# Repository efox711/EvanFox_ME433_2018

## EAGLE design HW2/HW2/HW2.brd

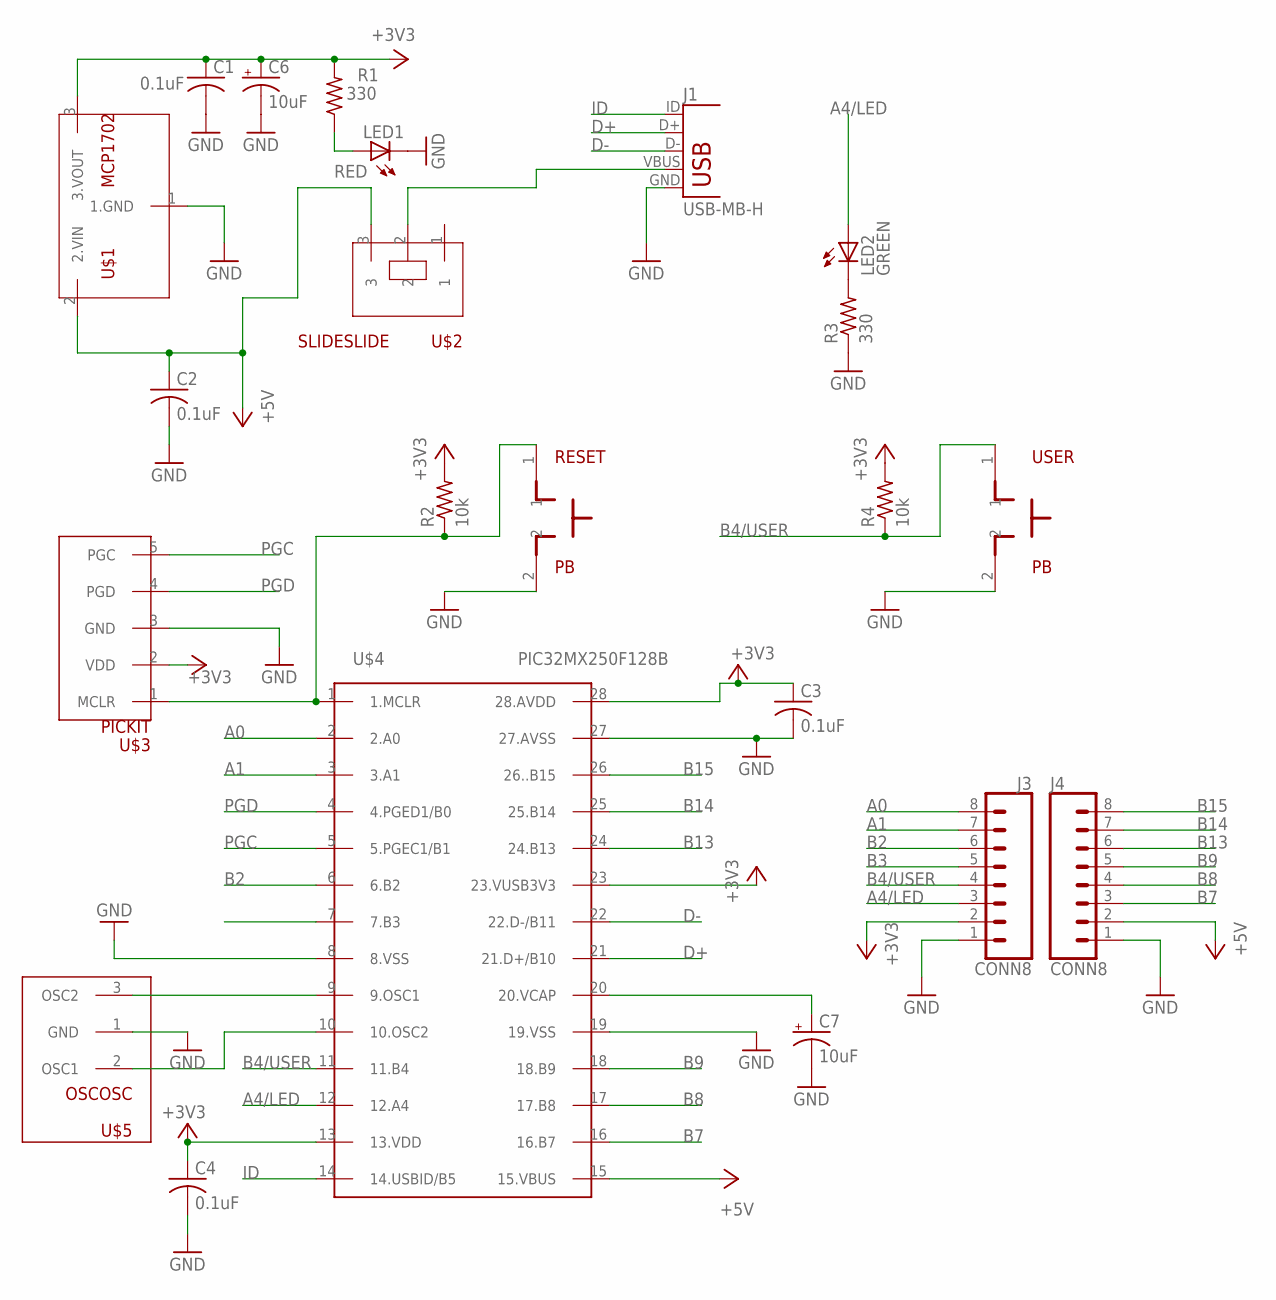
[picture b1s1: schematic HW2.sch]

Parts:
C1, C2, C3, C4: 0.1uF; C025-025X050
C6, C7: 10uF; B45181B
J1: USB-MB-H
J3, J4: CONN8; 1X08
LED1: RED; LED3MM
LED2: GREEN; LED3MM
R1, R3: 330; 0207/10
R2, R4: 10k; 0207/10
RESET: PB
U$1: MCP1702; TO92
U$2: SLIDESLIDE; SLIDE
U$3: PICKIT; 1X05
U$4: PIC32MX250F128B; DIL28-3
U$5: OSCOSC; OSC
USER: PB

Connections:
+3V3: C1.1, C3.1, C4.1, C6.+, J3.2, R1.2, R2.2, R4.2, U$1.3 (3.VOUT), U$3.2 (VDD), U$4.13 (13.VDD), U$4.23 (23.VUSB3V3), U$4.28 (28.AVDD)
+5V: C2.1, J4.2, U$1.2 (2.VIN), U$2.3, U$4.15 (15.VBUS)
A0: J3.8, U$4.2 (2.A0)
A1: J3.7, U$4.3 (3.A1)
A4/LED: J3.3, LED2.A, U$4.12 (12.A4)
B2: J3.6, U$4.6 (6.B2)
B3: J3.5, U$4.7 (7.B3)
B4/USER: J3.4, R4.1, U$4.11 (11.B4), USER.1
B7: J4.3, U$4.16 (16.B7)
B8: J4.4, U$4.17 (17.B8)
B9: J4.5, U$4.18 (18.B9)
B13: J4.6, U$4.24 (24.B13)
B14: J4.7, U$4.25 (25.B14)
B15: J4.8, U$4.26 (26..B15)
D+: J1.D+, U$4.21 (21.D+/B10)
D-: J1.D-, U$4.22 (22.D-/B11)
GND: C1.2, C2.2, C3.2, C4.2, C6.-, C7.-, J1.GND, J3.1, J4.1, LED1.K (C), R3.1, RESET.2, U$1.1 (1.GND), U$3.3 (GND), U$4.8 (8.VSS), U$4.19 (19.VSS), U$4.27 (27.AVSS), U$5.1 (GND), USER.2
ID: J1.ID, U$4.14 (14.USBID/B5)
unnamed: LED1.A, R1.1
unnamed: R2.1, RESET.1, U$3.1 (MCLR), U$4.1 (1.MCLR)
unnamed: LED2.K (C), R3.2
unnamed: J1.VBUS, U$2.2
unnamed: U$4.9 (9.OSC1), U$5.3 (OSC2)
unnamed: U$4.10 (10.OSC2), U$5.2 (OSC1)
unnamed: C7.+, U$4.20 (20.VCAP)
PGC: U$3.5 (PGC), U$4.5 (5.PGEC1/B1)
PGD: U$3.4 (PGD), U$4.4 (4.PGED1/B0)

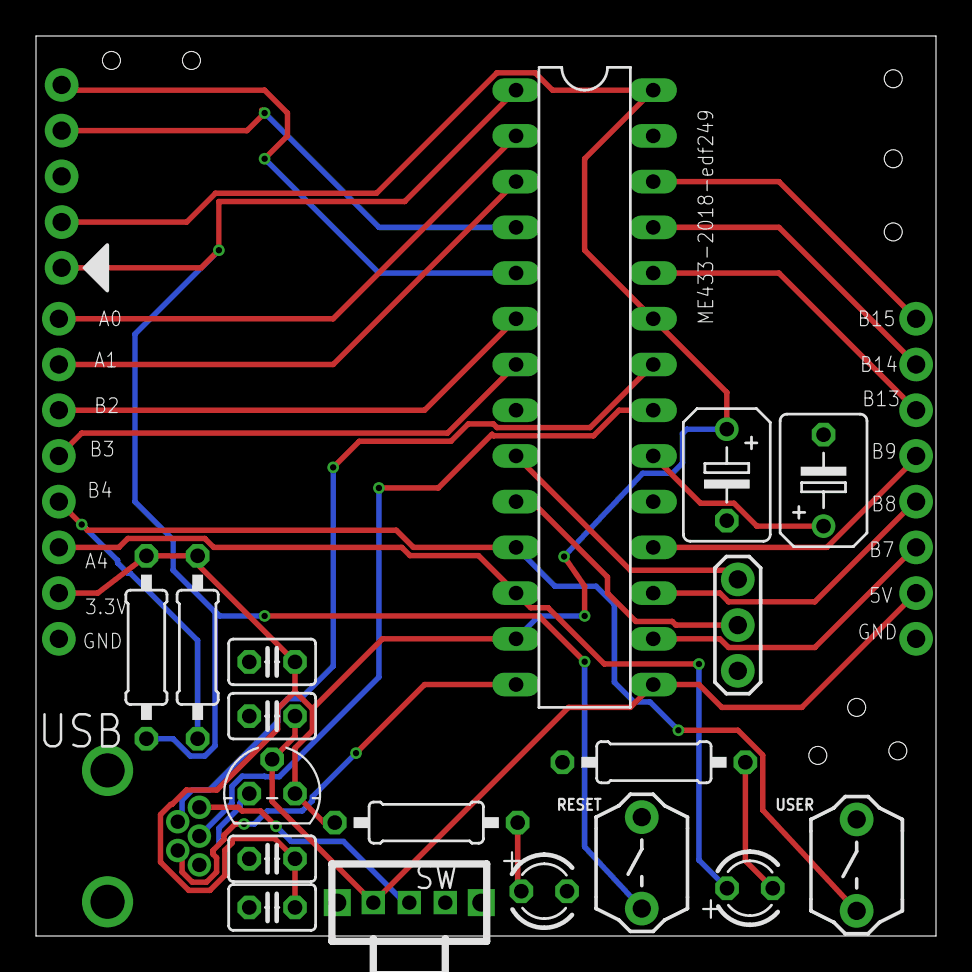
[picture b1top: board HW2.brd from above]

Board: 2 copper layers, 50.0 x 50.0 mm, 22 parts (0 on the bottom side), 27 nets.

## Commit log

2018-04-08 My first commit!
2018-04-08 Photos for HW1
2018-04-08 Renamed Images
2018-04-08 HW1 project made
2018-04-08 main.c made
2018-04-08 updated pragmas
2018-04-08 sign off update
2018-04-09 initialized LED and push button
2018-04-09 sign off
2018-04-09 sign in
2018-04-09 Functioning code!
2018-04-09 Added Demo
2018-04-10 Eagle Project Created for HW2
2018-04-10 Library updated, sign off
2018-04-10 more devices in Eagle
2018-04-11 sign on
2018-04-11 more devices added
2018-04-11 more devices
2018-04-11 working on schem
2018-04-12 check in
2018-04-12 schem update
2018-04-12 another update
2018-04-13 schematic finished
2018-04-14 update board
2018-04-15 added names
2018-04-15 complete, still needs error check
2018-04-15 aesthetic editing
2018-04-15 completed board
2018-04-15 DRC fixes
2018-04-15 gerbers made
2018-04-15 folder clean up
2018-04-15 Added board Images
2018-04-17 moved files around
2018-04-17 new HW4 project
2018-04-17 some code
2018-04-18 updated file locations
2018-04-19 added all functions
2018-04-19 first test
2018-04-19 test success
    output voltage is as anticipated
2018-04-19 messy sine wave, no triangle
2018-04-19 made HW5 project
2018-04-19 start of hw5, back to work on 4
2018-04-19 updated hw4 code
2018-04-19 running tests, sine wave not working
2018-04-19 timing working, 1ms loop
2018-04-19 sine wave working
2018-04-20 HW4 complete
2018-04-22 starting code
2018-04-22 set expander command
2018-04-23 cant get LED on, not working
2018-04-23 signing in
2018-04-24 singing on
2018-04-24 light turning on
2018-04-24 working code
2018-04-24 diagram and video
2018-04-24 name updated files
2018-04-25 setup hw6
2018-04-25 updated file orgs
2018-04-25 drawChar working
2018-04-25 darwstring working
2018-04-25 numbers increment properly
2018-04-25 functioning progress bar
2018-04-25 sign off, no fps
2018-04-25 added demo vid w/out fps
2018-04-27 doing some code
2018-04-27 pseudocode for init written
2018-04-29 Who am I works
2018-04-30 values outputting on screen, making bars function
2018-04-30 bars working
2018-04-30 functioning accel plotter with etch a sketch
2018-04-30 added demo vid
2018-05-03 restarting hw8
2018-05-03 HW1 code in harmony working
2018-05-03 HW9 created and tested with LED blinking
2018-05-03 HW8 working and complete
2018-05-08 replaced files with git ones
2018-05-10 working on HW9
2018-05-10 sending data with extra lines and r
2018-05-10 sending data with no char
2018-05-10 HW9 complete
2018-05-12 working on HW10
2018-05-12 working on MAF
2018-05-13 testing code
2018-05-13 no IIR, FIr and MAF working and plotted
2018-05-13 Doc and excel added
2018-05-13 updated files
2018-05-13 hw11 project made
2018-05-15 hw11 initial setup and hello world
2018-05-17 HW12 done
2018-05-17 HW13 built
2018-05-20 updated hw13
2018-05-21 HW11 completed
2018-05-24 starting HW14
2018-05-27 working on HW14
2018-05-27 pic code complete
2018-05-27 android project made
2018-05-27 HW14 complete
2018-05-29 HW15 on git
2018-05-29 took out cad files
2018-06-11 HW16 - wheels turning
2018-06-11 hw16 PI controller done
2018-06-11 moved to hw16
2018-06-12 HW17 working and complete, video to come
2018-06-12 hw17 organized w video
2018-06-12 everything complete besides android app merge
2018-06-12 ALL DONE!
2018-06-12 added photos and videos
